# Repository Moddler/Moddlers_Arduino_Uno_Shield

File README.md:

# Moddlers_Arduino_Uno_Shield
A generic Arduino Uno Shield template for KiCad

For some reason I did not realize a template existed in KiCAD, so I created one. Here it is.

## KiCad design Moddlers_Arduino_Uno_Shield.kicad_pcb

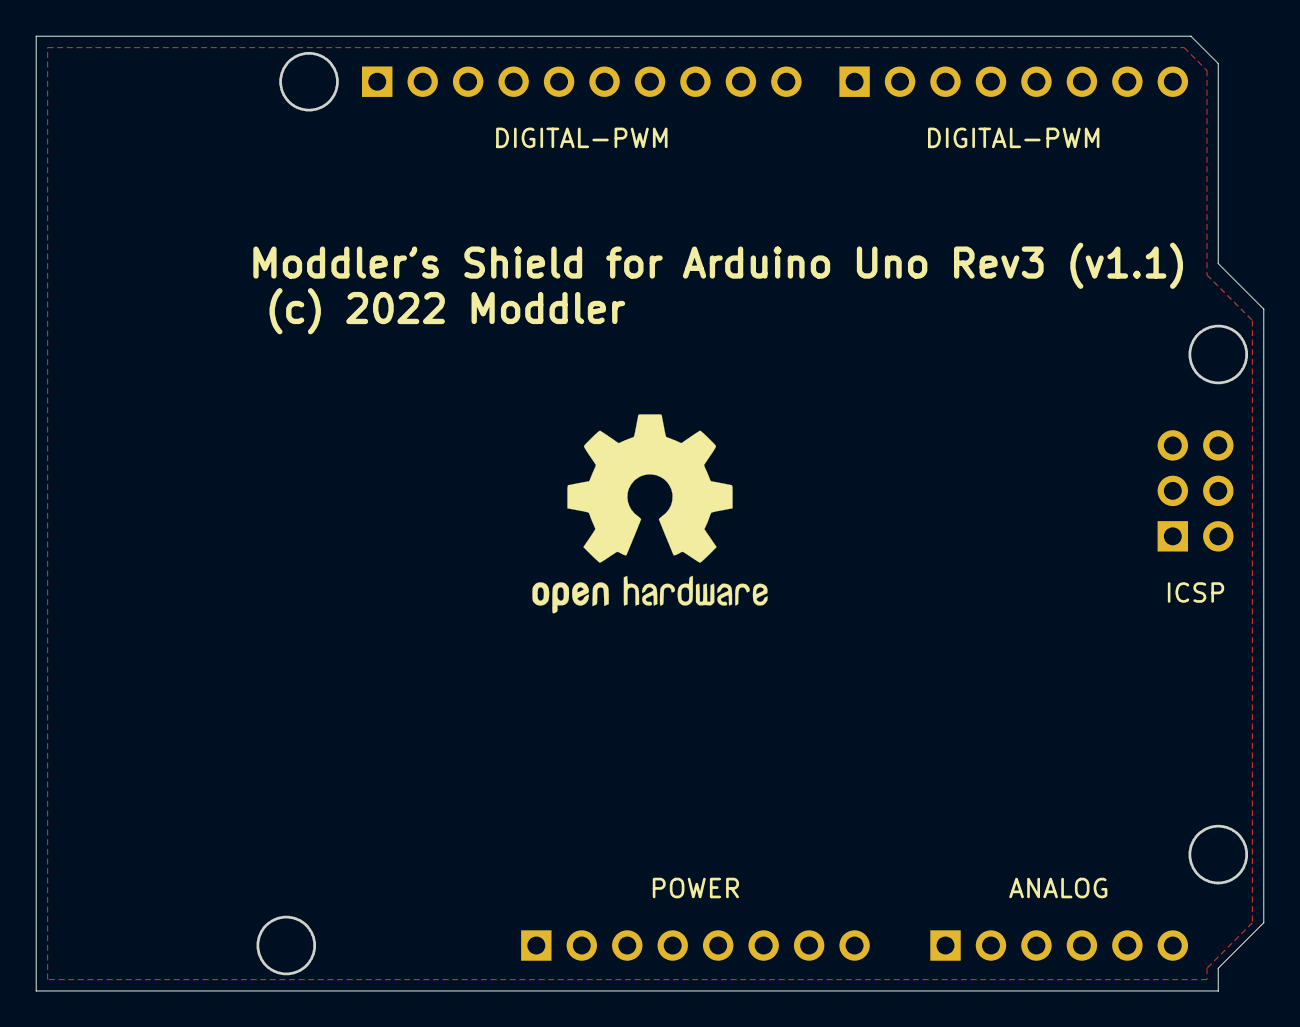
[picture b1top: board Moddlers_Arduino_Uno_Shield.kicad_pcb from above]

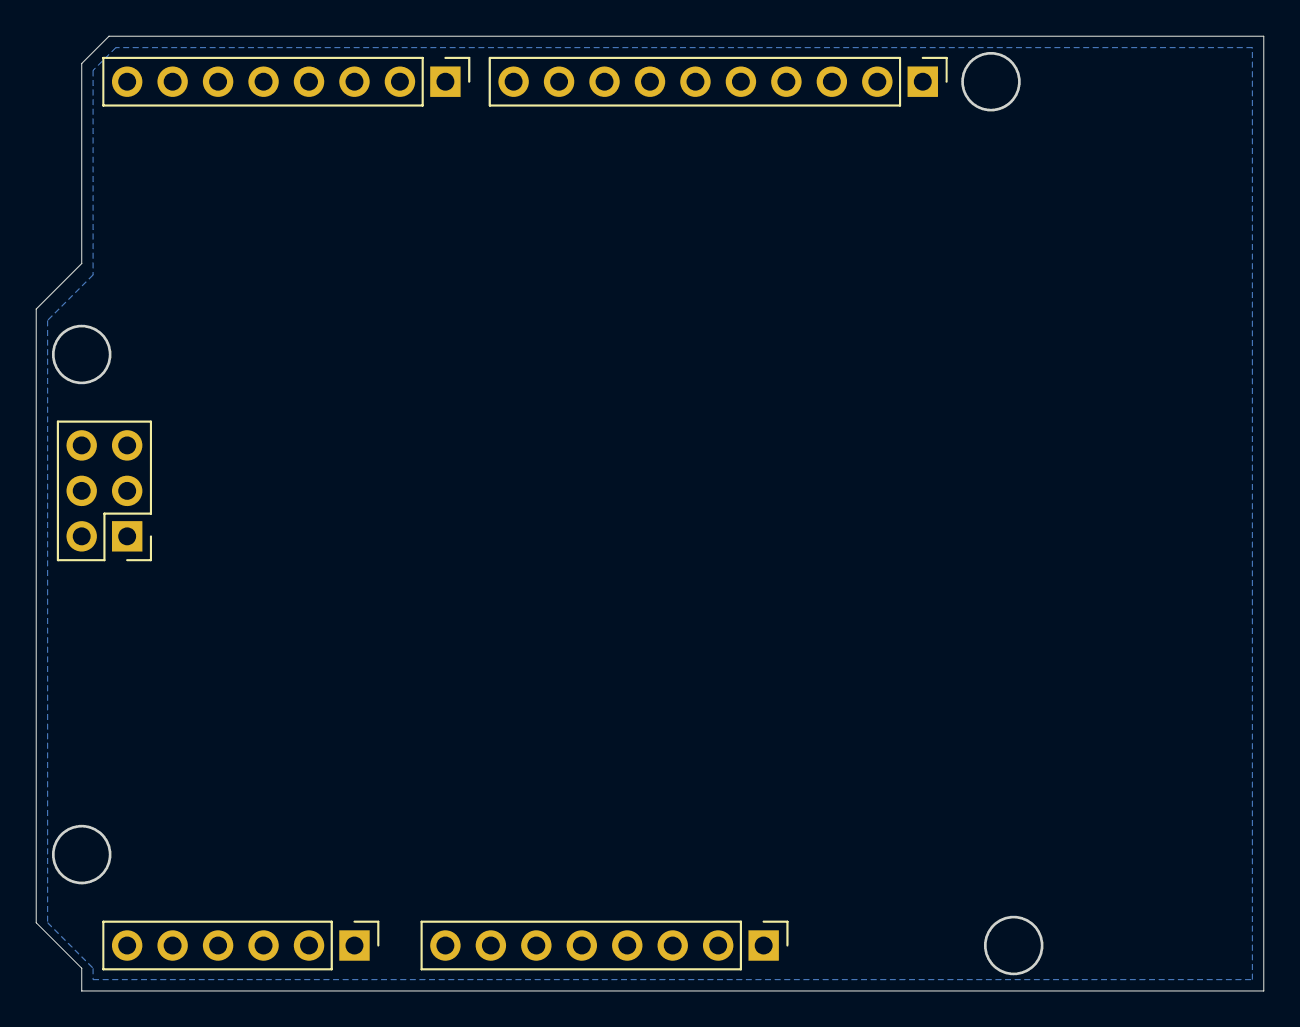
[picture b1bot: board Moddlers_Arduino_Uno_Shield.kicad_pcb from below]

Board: 2 copper layers, 68.5 x 53.2 mm, 5 parts (5 on the bottom side), 3 nets, no tracks yet.

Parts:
J1: POWER; PinHeader_1x08_P2.54mm_Vertical
J2: ANALOG; PinHeader_1x06_P2.54mm_Vertical
J3: DIGITAL-PWM; PinHeader_1x10_P2.54mm_Vertical
J4: DIGITAL-PWM; PinHeader_1x08_P2.54mm_Vertical
J5: ICSP; PinHeader_2x03_P2.54mm_Vertical

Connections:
+5V: J1.5, J5.6
/RESET: J1.3, J5.1
GND: J1.6, J1.7, J3.4, J5.2

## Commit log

2022-01-09 upload version 1.1
2022-01-31 Update to KiCAD Version 6

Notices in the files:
Moddlers_Arduino_Uno_Shield.kicad_pcb:
(c) 2022 Moddler
